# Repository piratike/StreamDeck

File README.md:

# StreamDeck
Development of Stream Deck based in Arduino Pro Micro with ATMega32u4

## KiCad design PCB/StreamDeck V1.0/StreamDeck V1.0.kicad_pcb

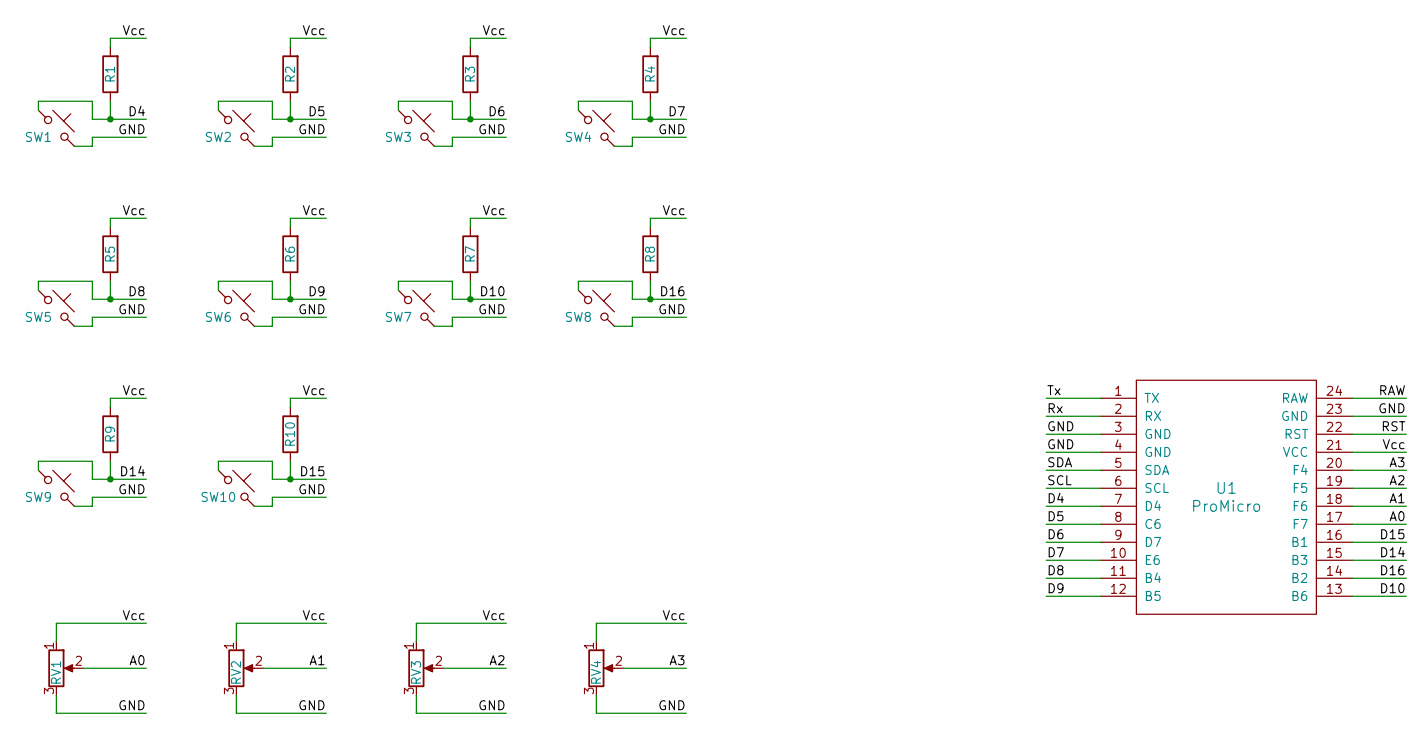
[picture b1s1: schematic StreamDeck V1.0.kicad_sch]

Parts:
R1, R2, R3, R4, R5, R6, R7, R8, R9, R10: 10k; R_1206_3216Metric
RV1, RV2, RV3, RV4: 10k; Potentiometer_TT_P0915N
SW1, SW2, SW3, SW4, SW5, SW6, SW7, SW8, SW9, SW10: SW_Push_45deg; SW_PUSH-12mm
U1: ProMicro

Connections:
/A0: RV1.2, U1.17 (F7)
/A1: RV2.2, U1.18 (F6)
/A2: RV3.2, U1.19 (F5)
/A3: RV4.2, U1.20 (F4)
/D4: R1.1, SW1.1, U1.7 (D4)
/D5: R2.1, SW2.1, U1.8 (C6)
/D6: R3.1, SW3.1, U1.9 (D7)
/D7: R4.1, SW4.1, U1.10 (E6)
/D8: R5.1, SW5.1, U1.11 (B4)
/D9: R6.1, SW6.1, U1.12 (B5)
/D10: R7.1, SW7.1, U1.13 (B6)
/D14: R9.1, SW9.1, U1.15 (B3)
/D15: R10.1, SW10.1, U1.16 (B1)
/D16: R8.1, SW8.1, U1.14 (B2)
/GND: RV1.3, RV2.3, RV3.3, RV4.3, SW1.2, SW2.2, SW3.2, SW4.2, SW5.2, SW6.2, SW7.2, SW8.2, SW9.2, SW10.2, U1.3 (GND), U1.4 (GND), U1.23 (GND)
/RAW: U1.24 (RAW)
/RST: U1.22 (RST)
/Rx: U1.2 (RX)
/SCL: U1.6 (SCL)
/SDA: U1.5 (SDA)
/Tx: U1.1 (TX)
/Vcc: R1.2, R2.2, R3.2, R4.2, R5.2, R6.2, R7.2, R8.2, R9.2, R10.2, RV1.1, RV2.1, RV3.1, RV4.1, U1.21 (VCC)

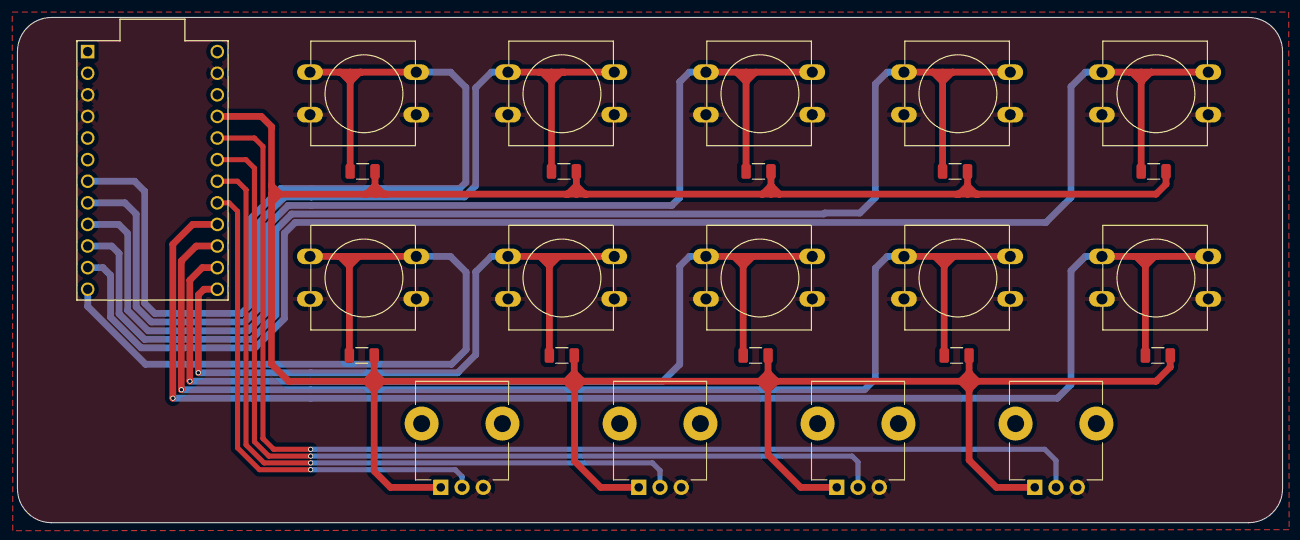
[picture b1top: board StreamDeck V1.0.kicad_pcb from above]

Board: 2 copper layers, 148.8 x 59.4 mm, 25 parts (0 on the bottom side), 16 nets.

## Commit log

2023-10-23 Added PCB developed with 10 switches, 4 potenciometers and an Arduino Pro Micro
2023-10-23 Added Arduino program for testing, need to develop a new one for the new Stream Deck done in the PCB
